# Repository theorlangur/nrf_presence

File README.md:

MCUBoot serial recovery:

speed issue:
changed ~/myapps/go/mynewt-mcumgr-cli/modified_mods/newtmgr@v0.0.0-20201028150837-60b2da78788c/nmxact/nmserial/serial_xport.go
specifically changed Sleep from 20ms to 1ms (there's one such sleep)
this upped transfer rate from ~ 830 bytes/s to ~ 4.5kb/s

speed issue update:
using mcumgr-client (rust-based tool), changed mtu to 4k and line input size to 8k
tweaked amount of retries + subsequent timeout duration (16 retries, 1000ms timeout)
and I'm getting an ok speed of ~ 6kb/s

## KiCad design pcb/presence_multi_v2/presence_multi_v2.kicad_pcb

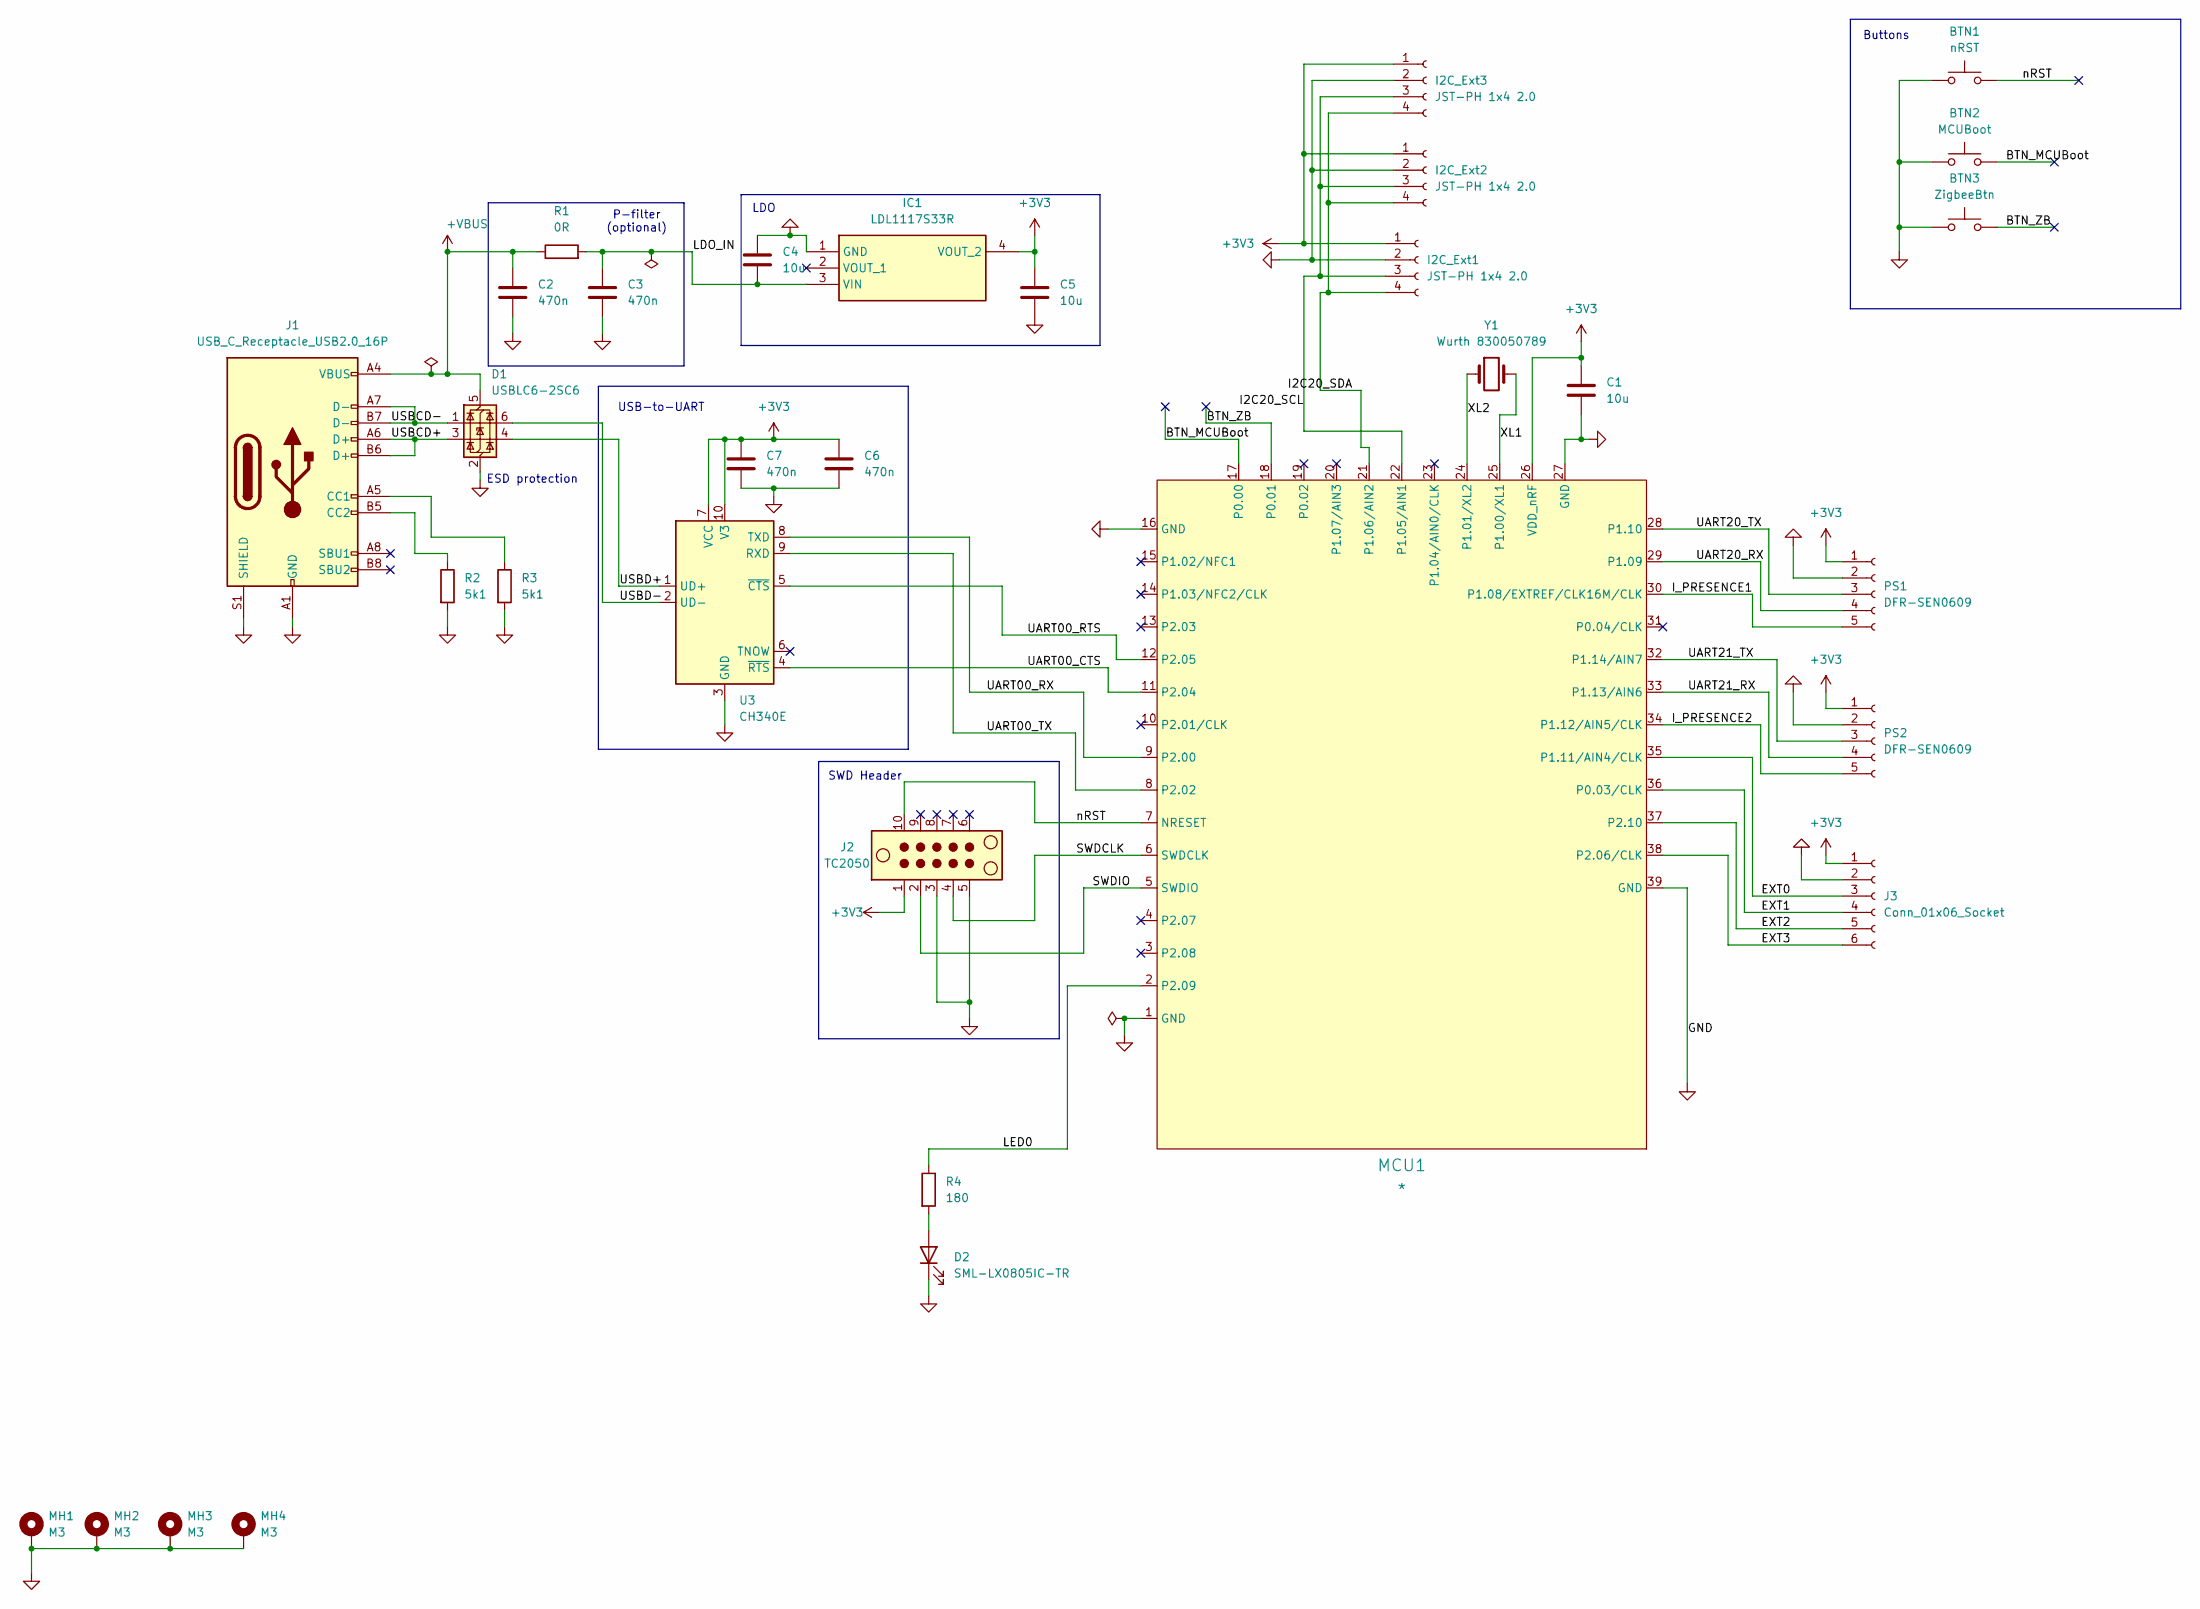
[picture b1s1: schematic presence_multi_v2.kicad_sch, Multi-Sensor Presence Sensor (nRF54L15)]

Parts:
BTN1: nRST; SW_SPST_TS-1088-xR020
BTN2: MCUBoot; SW_SPST_TS-1088-xR020
BTN3: ZigbeeBtn; SW_SPST_TS-1088-xR020
C1, C4, C5: 10u; C_0805_2012Metric
C2, C3, C6, C7: 470n; C_0805_2012Metric
D1: USBLC6-2SC6; SOT-23-6
D2: SML-LX0805IC-TR; LED_0805_2012Metric
I2C_Ext1, I2C_Ext2, I2C_Ext3: JST-PH 1x4 2.0; JST_PH_B4B-PH-K_1x04_P2.00mm_Vertical
IC1: LDL1117S33R; Mouser Part Number 511-LDL1117S33R
J1: USB_C_Receptacle_USB2.0_16P; USB_C_Receptacle_GCT_USB4105-xx-A_16P_TopMnt_Horizontal
J2: TC2050; Tag-Connect_TC2050-IDC-FP_2x05_P1.27mm_Vertical
J3: Conn_01x06_Socket; PinSocket_1x06_P2.54mm_Vertical
MCU1: *; Laird, BL54L15 Module, Platform Side
MH1, MH2, MH3, MH4: M3; MountingHole_3.5mm_Pad_Via
PS1, PS2: DFR-SEN0609; JST_PH_B5B-PH-K_1x05_P2.00mm_Vertical
R1: 0R; R_0805_2012Metric
R2, R3: 5k1; R_0805_2012Metric
R4: 180; R_0805_2012Metric
U3: CH340E; MSOP-10_3x3mm_P0.5mm
Y1: Wurth 830050789; Wurth-XTAL-830050789

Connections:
+3V3: C1.1, C5.1, C6.1, C7.1, I2C_Ext1.1, I2C_Ext2.1, I2C_Ext3.1, IC1.4 (VOUT_2), J2.1, J3.1, MCU1.26 (VDD_nRF), PS1.1, PS2.1, U3.7 (VCC), U3.10 (V3)
+VBUS: C2.1, D1.5 (VBUS), J1.A4 (VBUS), J1.A9 (VBUS), J1.B4 (VBUS), J1.B9 (VBUS), R1.1
/BTN_MCUBoot: BTN2.2, MCU1.17 (P0.00); also elsewhere on the board
/BTN_ZB: BTN3.2, MCU1.18 (P0.01); also elsewhere on the board
/EXT0: J3.3, MCU1.35 (P1.11/AIN4/CLK)
/EXT1: J3.4, MCU1.36 (P0.03/CLK)
/EXT2: J3.5, MCU1.37 (P2.10)
/EXT3: J3.6, MCU1.38 (P2.06/CLK)
/I2C20_SCL: I2C_Ext1.3, I2C_Ext2.3, I2C_Ext3.3, MCU1.22 (P1.05/AIN1)
/I2C20_SDA: I2C_Ext1.4, I2C_Ext2.4, I2C_Ext3.4, MCU1.21 (P1.06/AIN2)
/I_PRESENCE1: MCU1.30 (P1.08/EXTREF/CLK16M/CLK), PS1.5
/I_PRESENCE2: MCU1.34 (P1.12/AIN5/CLK), PS2.5
/LDO_IN: C3.1, C4.2, IC1.3 (VIN), R1.2
/LED0: MCU1.2 (P2.09), R4.1
/SWDCLK: J2.4, MCU1.6 (SWDCLK)
/SWDIO: J2.2, MCU1.5 (SWDIO)
/UART00_CTS: MCU1.11 (P2.04), U3.4 (~RTS)
/UART00_RTS: MCU1.12 (P2.05), U3.5 (~CTS)
/UART00_RX: MCU1.9 (P2.00), U3.8 (TXD)
/UART00_TX: MCU1.8 (P2.02), U3.9 (RXD)
/UART20_RX: MCU1.29 (P1.09), PS1.4
/UART20_TX: MCU1.28 (P1.10), PS1.3
/UART21_RX: MCU1.33 (P1.13/AIN6), PS2.4
/UART21_TX: MCU1.32 (P1.14/AIN7), PS2.3
/USBCD+: D1.3 (I/O2), J1.A6 (D+), J1.B6 (D+)
/USBCD-: D1.1 (I/O1), J1.A7 (D-), J1.B7 (D-)
/USBD+: D1.4 (I/O2), U3.1 (UD+)
/USBD-: D1.6 (I/O1), U3.2 (UD-)
/XL1: MCU1.25 (P1.00/XL1), Y1.2
/XL2: MCU1.24 (P1.01/XL2), Y1.1
/nRST: BTN1.2, J2.10, MCU1.7 (NRESET); also elsewhere on the board
GND: BTN1.1, BTN2.1, BTN3.1, C1.2, C2.2, C3.2, C4.1, C5.2, C6.2, C7.2, D1.2 (GND), D2.1 (K), I2C_Ext1.2, I2C_Ext2.2, I2C_Ext3.2, IC1.1 (GND), J1.A1 (GND), J1.A12 (GND), J1.B1 (GND), J1.B12 (GND), J1.S1 (SHIELD), J2.3, J2.5, J3.2, MCU1.1 (GND), MCU1.16 (GND), MCU1.27 (GND), MCU1.39 (GND), MH1.1, MH2.1, MH3.1, MH4.1, PS1.2, PS2.2, R2.2, R3.2, U3.3 (GND); also elsewhere on the board
unnamed: D2.2 (A), R4.2
unnamed: J1.A5 (CC1), R3.1
unnamed: J1.B5 (CC2), R2.1

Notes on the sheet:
SWD Header
ESD protection
P-filter (optional)
LDO
Buttons
USB-to-UART

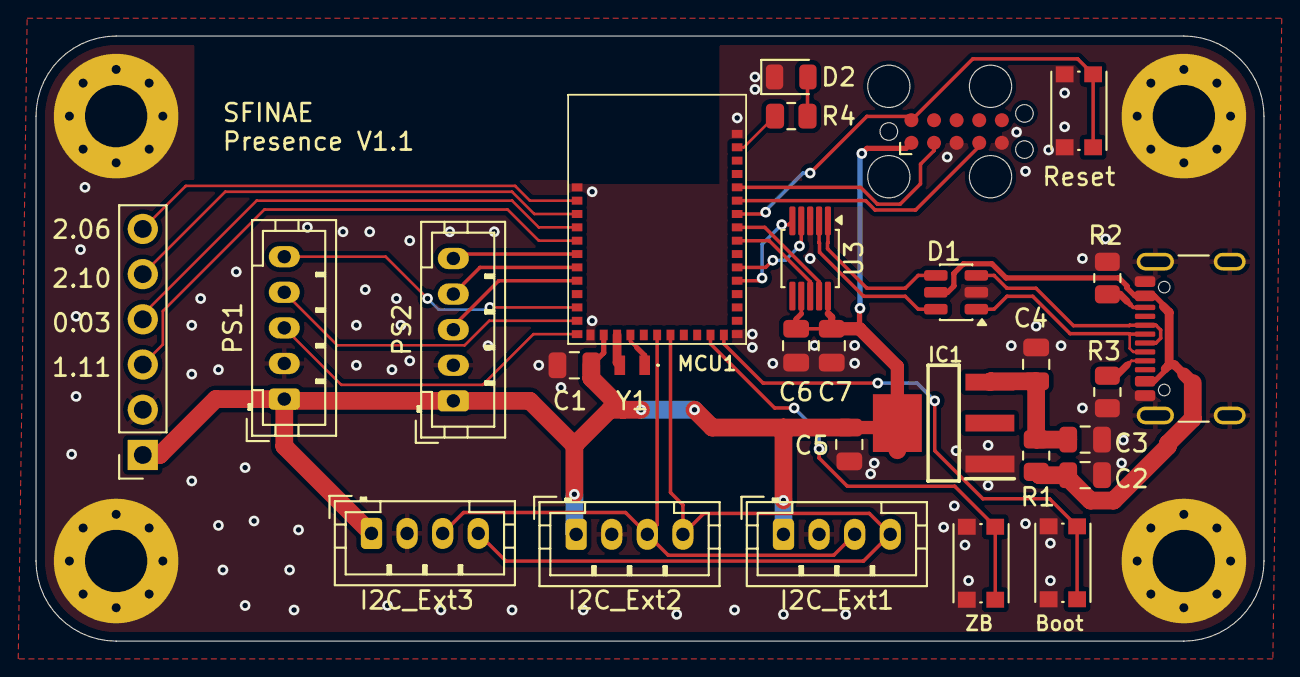
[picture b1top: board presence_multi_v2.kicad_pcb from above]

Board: 2 copper layers, 69.0 x 34.0 mm, 32 parts (0 on the bottom side), 35 nets.

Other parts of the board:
Boot: MCUBoot; SW_Push_1P1T_NO_CK_KMR2
Reset: nRST; SW_Push_1P1T_NO_CK_KMR2
ZB: ZigbeeBtn; SW_Push_1P1T_NO_CK_KMR2

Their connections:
/BTN_MCUBoot: Boot.2; also elsewhere on the board
/BTN_ZB: ZB.2; also elsewhere on the board
/nRST: Reset.2; also elsewhere on the board
GND: Boot.1, Reset.1, ZB.1; also elsewhere on the board

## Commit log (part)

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2025-12-13 initial commit (copy-paste from other project)
2025-12-13 added kicad folder with schematics and other stuff
2025-12-13 started actual PCB design
2025-12-14 replaced ASM1117 with LDL1117, removed 8 pin socket, added 3 4-pin JST-PH connectors
2025-12-15 added GND net with color, updated PCB
    imported GND net, imported MCUBoot color
2025-12-15 added a dedicated button for zigbee
2025-12-15 routing PCB
2025-12-16 ready version
2025-12-16 added info on components to a silkscreen
2026-01-09 added submodules
2026-01-09 minor change
2026-01-09 added building scripts
2026-01-09 refactored partitions piece into a separate dtsi file that's included in overlays
2026-01-09 added branch to bail out if no c4001 found
2026-01-09 refactored usb-to-uart into own dtsi
2026-01-09 added led blinking when dev not found
2026-01-09 MCUBoot: configured UART00 and using HW flow control
    important quirk: speed needs to be configured to 115200 so that the real
    speed 921600 can be used
2026-01-09 working version with MCUBoot
    had to adjust partition sizes
    MCUBoot partition is auto-calculated and the app offset is placed at a
    weird location
    adjusted atm the whole thing so that the slot0 is at 0xf800
    it works
    but 'list' command doesn't show any valid images
2026-01-09 added launch config for MCUBoot
2026-01-09 ok, the reason or baudrate mismatch is 128MHz clock frequence for uart00 instead of 16MHz
    so the requested 115200 are basically scaled up 8x to 921600
2026-01-09 tried to increase the speed... didn't really help for whatever reason
2026-01-09 added script to get uart output from usb-to-uart on board
2026-01-09 added a custom mcumgr and a short description + a script for image update
2026-01-10 another approach at MCUBoot serial recovery flashing
    using mcumgr-client with option tweaks (mcumgr_client_update.sh)
    and the final speed of about 6kb/s
2026-01-11 for whatever reason uart20 doesn't work well with pins 1.09 and 1.10 for rx/tx
    uart22 does
2026-01-11 circled back to uart20
    the reason was pinctrl misconfiguration
    original board pinctrl config provided pinconfig for uart20 in 2 groups
    with CTS pin and a different RX pin
    harmonized
2026-01-11 added 1 check for validity of uart
2026-01-12 changed z2m converter
    * fixed issue with wrong 'key' type (ought to be an array)
    * using 'configure' entry per cluster
2026-01-12 using cmake-way to use submodule libraries
2026-01-12 added save/reset config to c4001 cluster description
2026-01-12 added logic to reset zigbee when zigbee button is hold when reset
2026-01-12 initializing occupancy at start
2026-01-13 added configuration for i2c, added environment fetching
    using i2c21 instance since uart20 is already in use
    added clusters for temp/humidity/co2/tvoc/aqi
2026-01-13 forgot to start led thread
    also giving time for led to blink
2026-01-13 not waiting
2026-01-13 increased timeout, using udev rule to reference usb-to-uart ch340
2026-01-13 using existing helpers instead of making own cluster modern extend stuff
2026-01-14 added 'Cortex-Debug' extension and enabled thread info
    finally I can see stack traces of all threads...
2026-01-18 moved cortex-debugger to a vscode-wide settings
2026-01-18 refactored c4001 so that it's possible to have several instances of it + added 2nd such instance in overlay DTS
2026-01-18 added 2nd endpoint with auxiliary c4001 (not in use yet)
2026-01-18 enabled 2nd EP and added support for 2nd C4001 presence sensor
2026-01-18 2 c4001 sensors compile and run, as also 2 endpoints
2026-01-18 using dedicated symlink for running minicom for uart
2026-01-18 rewrote external converter to use only modern helpers
    status cluster stayed as it was
    c4001Config -> c4001Cmds
2026-01-31 PCB: adjsuted DRU (were too strict)
2026-01-31 PCB: re-arranged the whole board
    made it significantly smaller
    used a slightly different footprint for buttons
    USB-C should be placed symmetrically now
2026-02-02 fixed bug with a presence logic
    pin 2 was ignored basically
2026-02-02 fixing external converter
2026-02-03 explicitly specifying read-write options for attributes
    this was the reason for failed attribute writes
2026-02-04 left one slot partition, increased the size of it
    was needed for dbg zigbee
2026-02-04 removed explicit 'medium mem config'
2026-02-04 increased resources for zigbee in attempt to fix stability of the device in router mode
2026-02-06 this all probably doesn't play a role since the actual problem is in endless broadcasting and requesting for addresses
2026-02-07 back to default router settings
2026-02-08 added nrf_uart lib as a submodule
2026-02-08 using nrf_uart lib as a submodule
2026-02-08 switched to RTT loggin
2026-02-08 added LD2412 testing code. seems to work
2026-02-09 defined ld2412 zigbee cluster
2026-02-09 extending ld2412 zigbee cluster with statistical information
2026-02-11 updated nrf_uart submodule
2026-02-11 added PIR sensor logic
2026-02-14 minor refactoring
2026-02-14 started working on ld2412 task
2026-02-14 implementing requests to LD2412 task
    implemented snapshotting the collected statistics
    also the sensor is put into engineering mode from the start
    (needed for light sensing, energy config)
2026-02-14 implemented all async requests to LD2412 task
2026-02-14 removed c4001. ld2412 is not properly supported yet
    various blocks of code are commented out
    but it's buildable
2026-02-14 combined several attributes of ld2412 cluster into composed structures
    using OctetStr as a type though, not struct
    it's not clear how to properly use 'struct'
    added validation for various types
2026-02-15 implementing missing parts...
    on_get_stat_snapshot, on_back_analysis_done
    added get_data_for_ld2412, get_zb_ep_for_ld2412 helpers to get
    zb_ep/data structs depending on actual instance
2026-02-15 more work towards working ld2412 logic
    * added 'update_*' functions to update zigbee attributes from actual
    state of the device
    * implemented error handling for changing parameters
    * implemented initial configuration assignment on the start
2026-02-15 provided setters for both instances
2026-02-15 removed tx power control
2026-02-15 re-worked interrupt processing
    all goes via 1 ISR
    PIR is dominant for detection
    but secondary for holding
2026-02-16 minor cleanup
2026-02-16 forgot to revert uart speed back to 9600
2026-02-22 renamed model to ld2412, changed z2m converter
    added ai-generated cluster description
    adjusted ld2412-ng.js to use the cluster description
    z2m can at least load it
2026-02-22 aux ld2412 had wrong uart speed
2026-02-22 z2m converter fixes
    * it should configure correctly now without errors (changed octet str to
    char str because of nordic's bug in zigbee)
    * it reads correctly data, also for composites
2026-02-22 fixing initial presence evaluation
2026-02-22 minor fix
2026-02-22 cleanup
2026-02-22 fixing setting composite entities
2026-02-22 added notification when various set cfg is done
2026-02-22 updated uart submodule
2026-02-23 properly initializing thresholds + printing on change
2026-02-23 added print statements
2026-02-23 added printing of stats
2026-02-23 added support for char str in converter
2026-02-23 energy statistics is non-reportable, can only be read
2026-02-23 energy stat is back to octet string + composite feature
2026-02-25 trying to get zboss trace logging...
2026-02-28 increased allow sample count for statistic to 255, updated ld2412 submodule
2026-03-05 disabled zigbee uart traces
2026-03-05 changing mode back to router
    hoping with libzboss fixed (sending to bound) it'll behave
    nicely
2026-03-10 added logging of presence changes
2026-03-11 using 'status2' to convey any state changes of each presence piece
2026-03-14 better tracking of stats
2026-03-14 gemini: added explicit targetEntity resolution for multi-endpoint
    no idea if that's how it supposed to be
2026-03-14 improved logging lines
2026-03-14 gemini: avoiding double-ep config
2026-03-15 this seems to stabilize operating of the device as a router
    with defaults I was observing weird leave-rejoin behavior and delayed
    reactions
2026-03-15 updated zb submodule
2026-03-15 End-Device seems to be more stable than router unfortunately
2026-03-15 fixed a bug
    all but bit 0 should've been erased
2026-03-20 added minimum initial clear time (3 sec)
    decoupled from clear times of ld2412 modules
2026-04-04 added missing names for attributes and clusters
    otherwise z2m malfunctions and some attributes are not changed properly
2026-04-04 changed PCB thickness, changed origin (better integration with FreeCAD)
2026-04-04 disabled network buffre count change
2026-04-05 fixed z2m js: IID->ID
2026-05-17 using zigbee string's 'capacity' + added ultimate zb failure handler
2026-05-17 using latest
2026-05-22 using atomics to reduce the amount of zb_schedule_app_callback calls
    g_PresenceChangeState: unset state is 0; it's or-ed in 'changed' flags
    and simply added last state. CAS-loop to set/add atomically latest
    change state before it was processed by zigbee thread
    g_PresenceHWState: last real presence registered state to be processed
    by send_on_off. 'val' passed to send_on_off says if the request is from
    a real presence or not (based on the OnOffVirtualMask)
2026-05-22 increased scheduler queue size to 96
    suspicion is: at some point it gets an overflow
2026-05-23 adding atomics to combine multiple frequent changes of presence state didn't help
    this commit attempts to flood-gate sending zigbee commands and changes
    basically I'm not allowing sending on/off commands and a presence attribute
    change more often than kZigbeeFloodProtectionTimeout milliseconds.
    g_DelayedVal is not atomic since reading/writing there happens only from
    zigbee thread
2026-05-24 turning on coredumps to flash and switched to fully static partition management
    otherwise the system didn't want to add the coredump_partition although
    it was defined in partitions.dtsi
2026-05-25 enabled shell support with coredumps
2026-05-25 added querying coredump and an artificial crash to store one
2026-05-28 removed coredump testing code,
    left only setting bit for 'has coredump'
    in status3
2026-05-31 added watchdog tracking
    interval set to 2 seconds
    feeding every 500ms
    when timeout comes -> feed one last time and k_oops to write coredump
2026-06-05 storing coredump directly, instead of k_oops
2026-06-14 updated nrf_zb_cpp pointer
2026-06-19 deleted outdated ai_ld2412.js
    it stays in the git history anyways
2026-06-21 part of refactoring
2026-06-21 updated .gitignore
2026-06-21 updated nrf_zb_cpp submodule
2026-06-21 tvoc -> voc to get 'measurement' class on HA and graphs
2026-06-27 added configs for building with experimental gcc16.1 toolchain
    had to fix several compiler errors (casting from packed struct members)
    added also tasks to run VSCode with a proper environment
2026-06-28 let static reflection madness begin
2026-06-28 refactoring. it's buildable again
2026-06-29 configured launch entries or NRF-connect
2026-06-29 changed watchdog strategy
    nordic's hardware watchdog bites
    if it was fired I have mere tens of microseconds to do something
    it's not enough to write a coredump
    so 2-stage watchdog scheme is used: task watchdog from zephyr based on
    the timers + hw watchdog as a last-hope-fallback to reset
    also added '-fno-omit-frame-pointer' when coredumps are enabled
2026-06-29 'coredump.bin' shall not be part of the git
2026-06-29 added a bool to control the dog feeding
2026-06-29 added status command1 support to z2m converter
2026-06-29 qwen 3.6: expanded status1/2/3 with their actual meanings and descriptions
2026-06-30 added memfault integration, removed zephyr's coredump
    problem: zephyr's coredump cannot be properly written when
    radio is active (MPSL screws stuff up)
    memfault allegedly does better
    to be seen...
2026-06-30 fix for 'stop feeding watchdog' z2m command
    it's done via e.enum()
2026-06-30 re-wrote coredump scripts to memfault
    but I will be reverting this back in a moment...
2026-06-30 back to 2-stage watchdog + bigger timeouts
